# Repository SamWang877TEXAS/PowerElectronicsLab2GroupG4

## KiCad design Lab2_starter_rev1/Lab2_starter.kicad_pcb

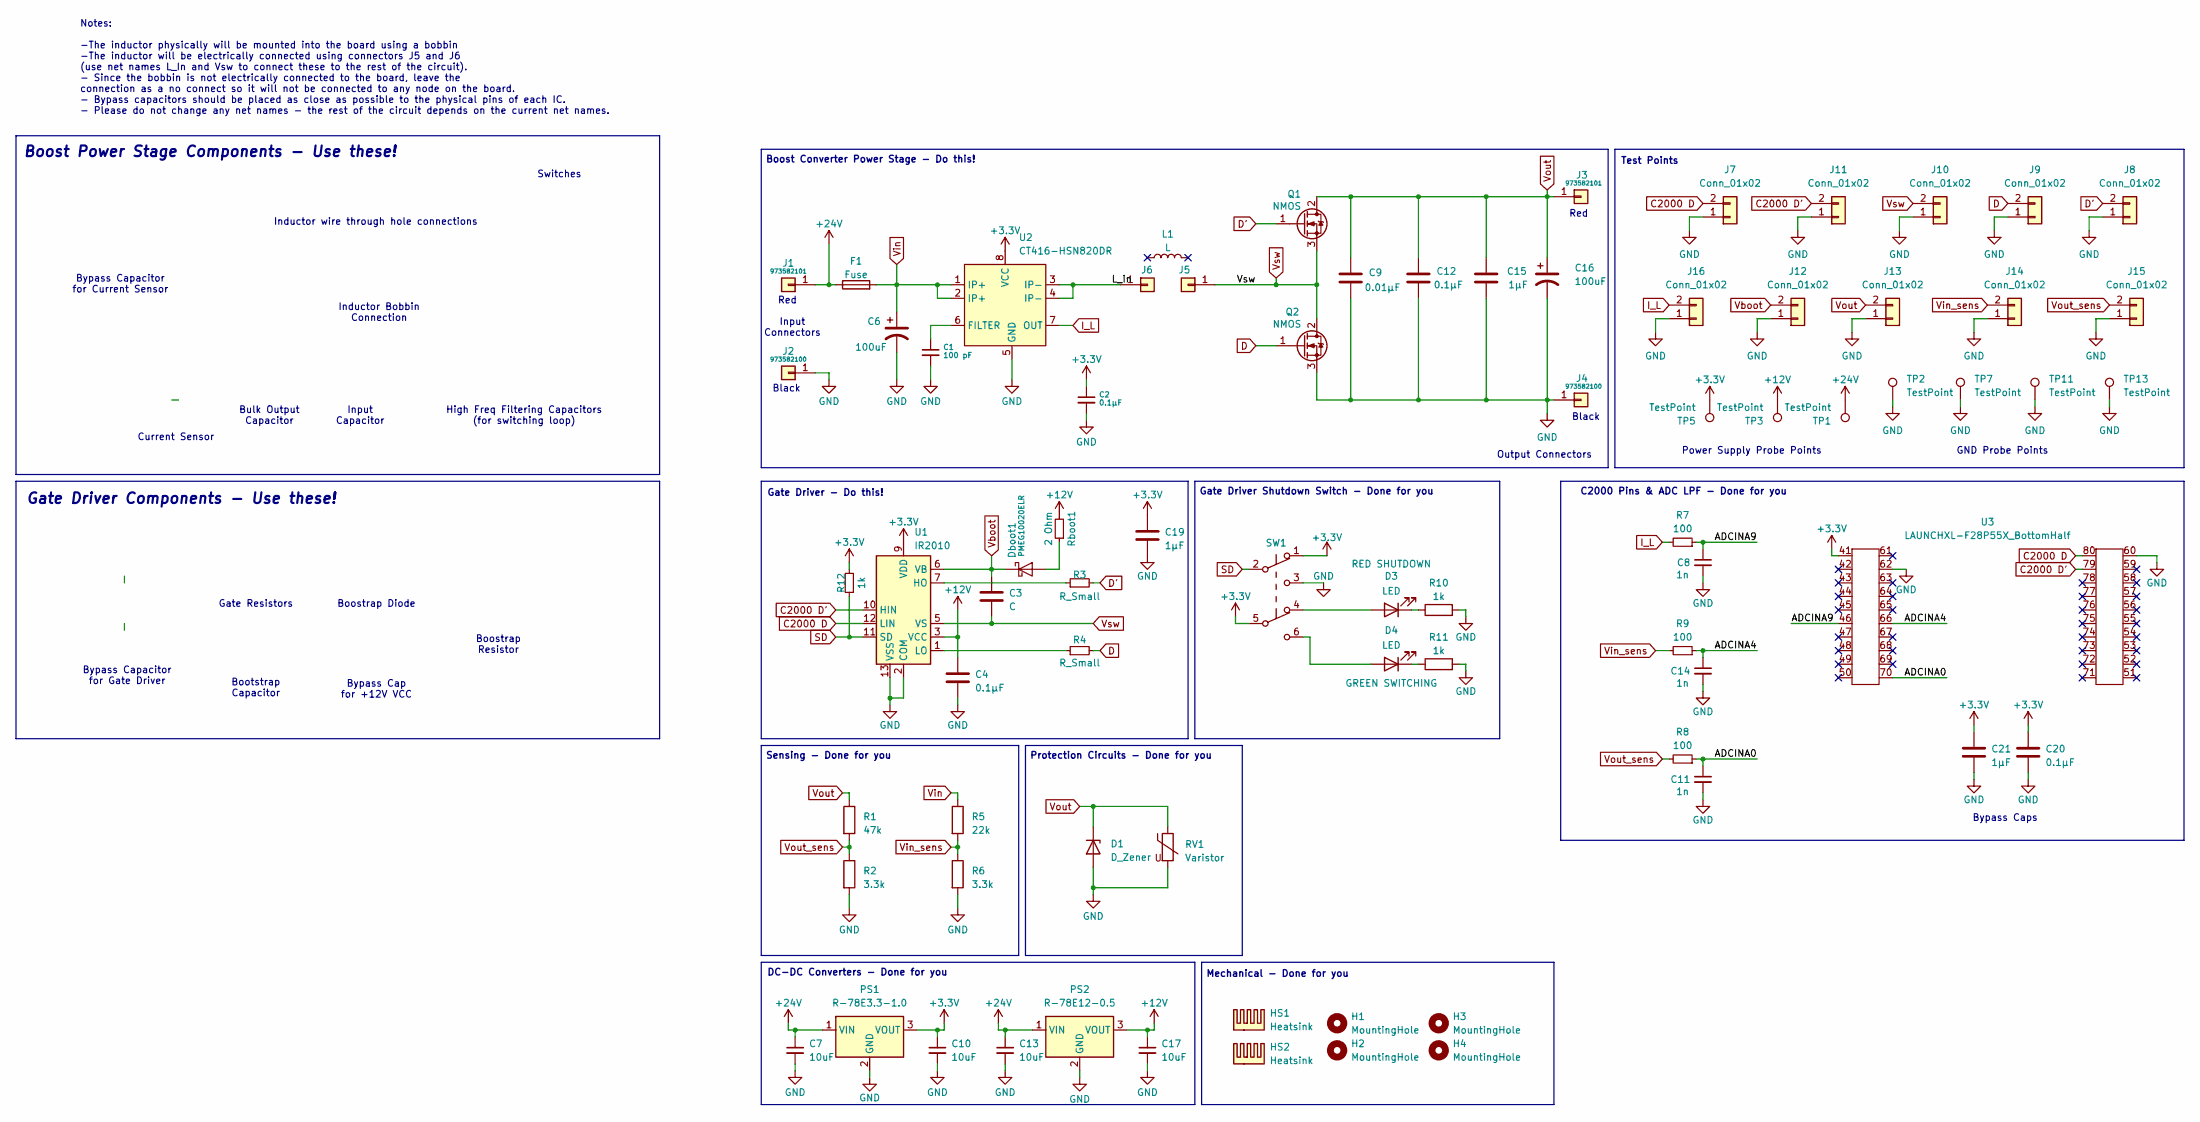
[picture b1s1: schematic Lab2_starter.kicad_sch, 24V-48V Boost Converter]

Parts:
C1: 100 pF; C_0805_2012Metric
C2, C4, C12, C20: 0.1μF; C_0805_2012Metric
C3: C; C_0805_2012Metric
C6, C16: 100uF; 16PX2200MEFC10X20
C7, C10, C13, C17: 10uF; C_0805_2012Metric
C8, C11, C14: 1n; C_0805_2012Metric
C9: 0.01μF; C_0805_2012Metric
C15, C19, C21: 1μF; C_0805_2012Metric
D1: D_Zener; 1.5KE75A
D3, D4: LED; WL-SMRW_1206_REC
Dboot1: PMEG10020ELR; Nexperia_CFP3_SOD-123W
F1: Fuse; 696108003002
H1, H2, H3, H4: MountingHole; MountingHole_3.2mm_M3
HS1, HS2: Heatsink; HSS-B20-NPS-01
J1, J3: 973582101
J2, J4: 973582100
J5, J6: Conn_01x01; Inductor_wire_conn
J7, J8, J9, J10, J11, J12, J13, J14, J15, J16: Conn_01x02; TP
L1: L; Inductor
PS1: R-78E3.3-1.0; PARTREV 6
PS2: R-78E12-0.5; R-78E-0.5_RCP
Q1, Q2: NMOS; TO-220-3_Vertical
R1: 47k; R_0805_2012Metric
R2, R6: 3.3k; R_0805_2012Metric
R3, R4: R_Small; R_0805_2012Metric
R5: 22k; R_0805_2012Metric
R7, R8, R9: 100; R_0805_2012Metric
R10, R11, R12: 1k; R_0805_2012Metric
RV1: Varistor; V100ZA15P
Rboot1: 2 Ohm; R_0805_2012Metric
SW1: SW_Push_DPDT; SLW1116297AD
TP1, TP2, TP3, TP5, TP7, TP11, TP13: TestPoint; TestPoint_Loop_D1.80mm_Drill1.0mm_Beaded
U1: IR2010; 1-2199298-3
U2: CT416-HSN820DR; SOIC-8_3.9x4.9mm_P1.27mm
U3: LAUNCHXL-F28P55X_BottomHalf

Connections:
+3.3V: C2.1, C10.1, C19.1, C20.1, C21.1, PS1.3 (VOUT), R12.2, SW1.1 (A), SW1.5 (B), TP5.1, U1.9 (VDD), U2.8 (VCC), U3.41
+12V: C4.1, C17.1, PS2.3 (VOUT), Rboot1.2, TP3.1, U1.3 (VCC)
+24V: C7.1, C13.1, F1.1, J1.1, PS1.1 (VIN), PS2.1 (VIN), TP1.1
/ADCINA0: C11.1, R8.1, U3.70
/ADCINA4: C14.1, R9.1, U3.66
/ADCINA9: C8.1, R7.1, U3.46
C2000 D: J7.2, U1.12 (LIN), U3.80
C2000 D': J11.2, U1.10 (HIN), U3.79
D: J9.2, Q2.1 (G), R4.2
D': J8.2, Q1.1 (G), R3.2
GND: C1.2, C2.2, C4.2, C6.2, C7.2, C8.2, C9.2, C10.2, C11.2, C12.2, C13.2, C14.2, C15.2, C16.2, C17.2, C19.2, C20.2, C21.2, D1.2 (A), J2.1, J4.1, J7.1, J8.1, J9.1, J10.1, J11.1, J12.1, J13.1, J14.1, J15.1, J16.1, PS1.2 (GND), PS2.2 (GND), Q2.3 (S), R2.2, R6.2, R10.2, R11.2, RV1.2, SW1.3 (C), TP2.1, TP7.1, TP11.1, TP13.1, U1.2 (COM), U1.13 (VSS), U2.5 (GND), U3.60, U3.62
I_L: J16.2, R7.2, U2.7 (OUT)
unnamed: D3.2 (A), SW1.4 (A)
unnamed: D3.1 (K), R10.1
unnamed: D4.2 (A), SW1.6 (C)
unnamed: D4.1 (K), R11.1
unnamed: Dboot1.2 (A), Rboot1.1
unnamed: J6.1, U2.3 (IP-), U2.4 (IP-)
unnamed: R3.1, U1.7 (HO)
unnamed: R4.1, U1.1 (LO)
unnamed: C1.1, U2.6 (FILTER)
SD: R12.1, SW1.2 (B), U1.11 (SD); also elsewhere on the board
Vboot: C3.1, Dboot1.1 (K), J12.2, U1.6 (VB)
Vin: C6.1, F1.2, R5.1, U2.1 (IP+), U2.2 (IP+)
Vin_sens: J14.2, R5.2, R6.1, R9.2
Vout: C9.1, C12.1, C15.1, C16.1, D1.1 (K), J3.1, J13.2, Q1.2 (D), R1.1, RV1.1
Vout_sens: J15.2, R1.2, R2.1, R8.2
Vsw: C3.2, J5.1, J10.2, Q1.3 (S), Q2.2 (D), U1.5 (VS)

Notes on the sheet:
High Freq Filtering Capacitors (for switching loop)
Inductor wire through hole connections
Input Connectors
Sensing - Done for you
Protection Circuits - Done for you
Input Capacitor
Test Points
Bypass Cap for +12V VCC
Black
Mechanical - Done for you
Red
Bulk Output Capacitor
Power Supply Probe Points
Bootstrap Capacitor
Gate Driver Shutdown Switch - Done for you
Notes: -The inductor physically will be mounted into the board using a bobbin -The inductor will be electrically connected using connectors J5 and J6 (use net names L_In and Vsw to connect these to the rest of the circuit). - Since the bobbin is not electrically connected to the board, leave the co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
Gate Driver - Do this!
Current Sensor
Boostrap Resistor
DC-DC Converters - Done for you
Boost Power Stage Components - Use these!
Gate Resistors
C2000 Pins & ADC LPF - Done for you
Boostrap Diode
Output Connectors
Bypass Capacitor for Current Sensor
Inductor Bobbin Connection
Switches
Bypass Capacitor for Gate Driver
Gate Driver Components - Use these!
GND Probe Points
Bypass Caps
Boost Converter Power Stage - Do this!

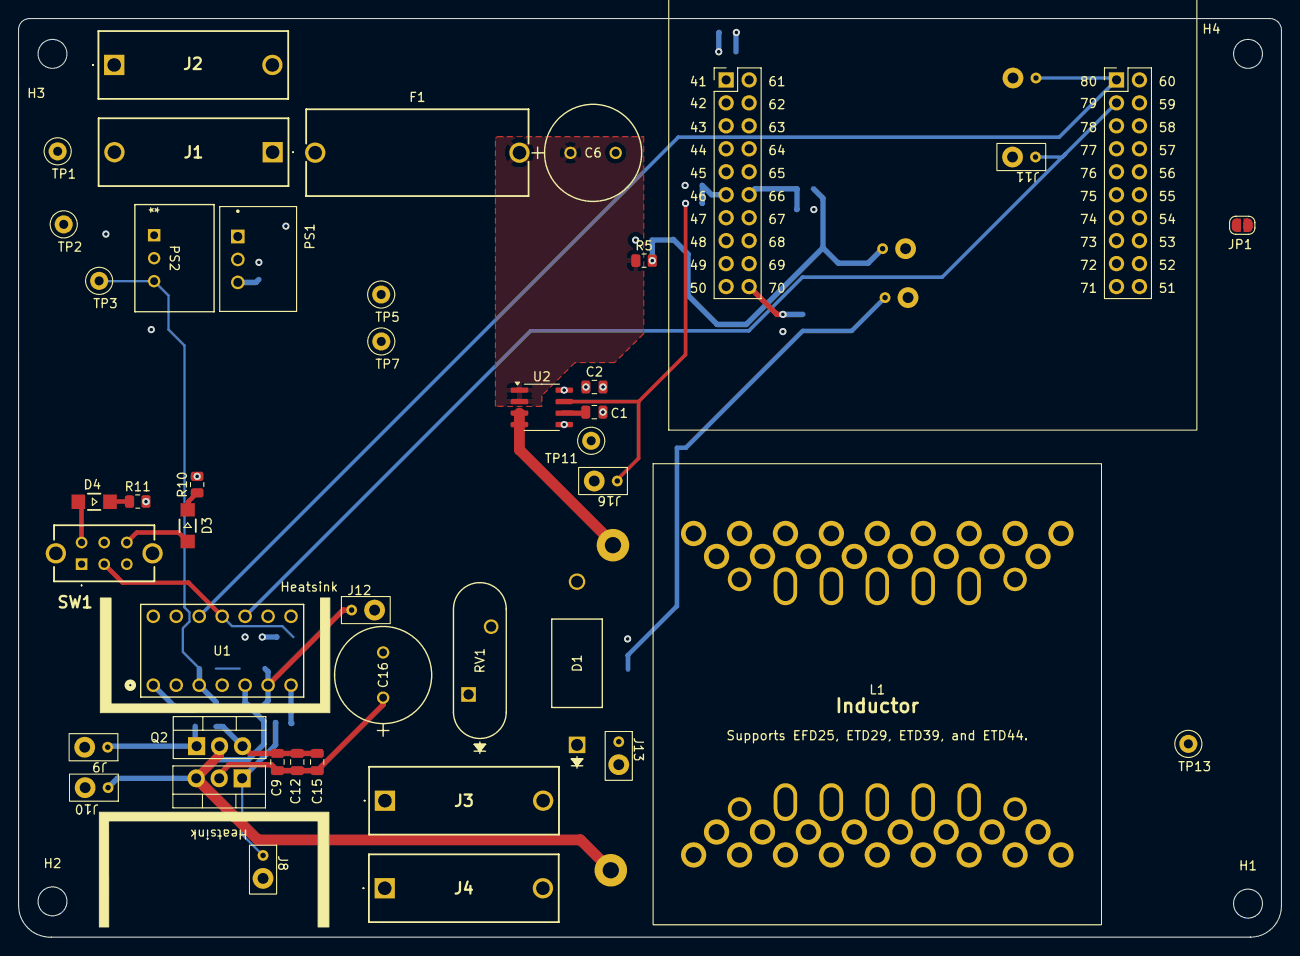
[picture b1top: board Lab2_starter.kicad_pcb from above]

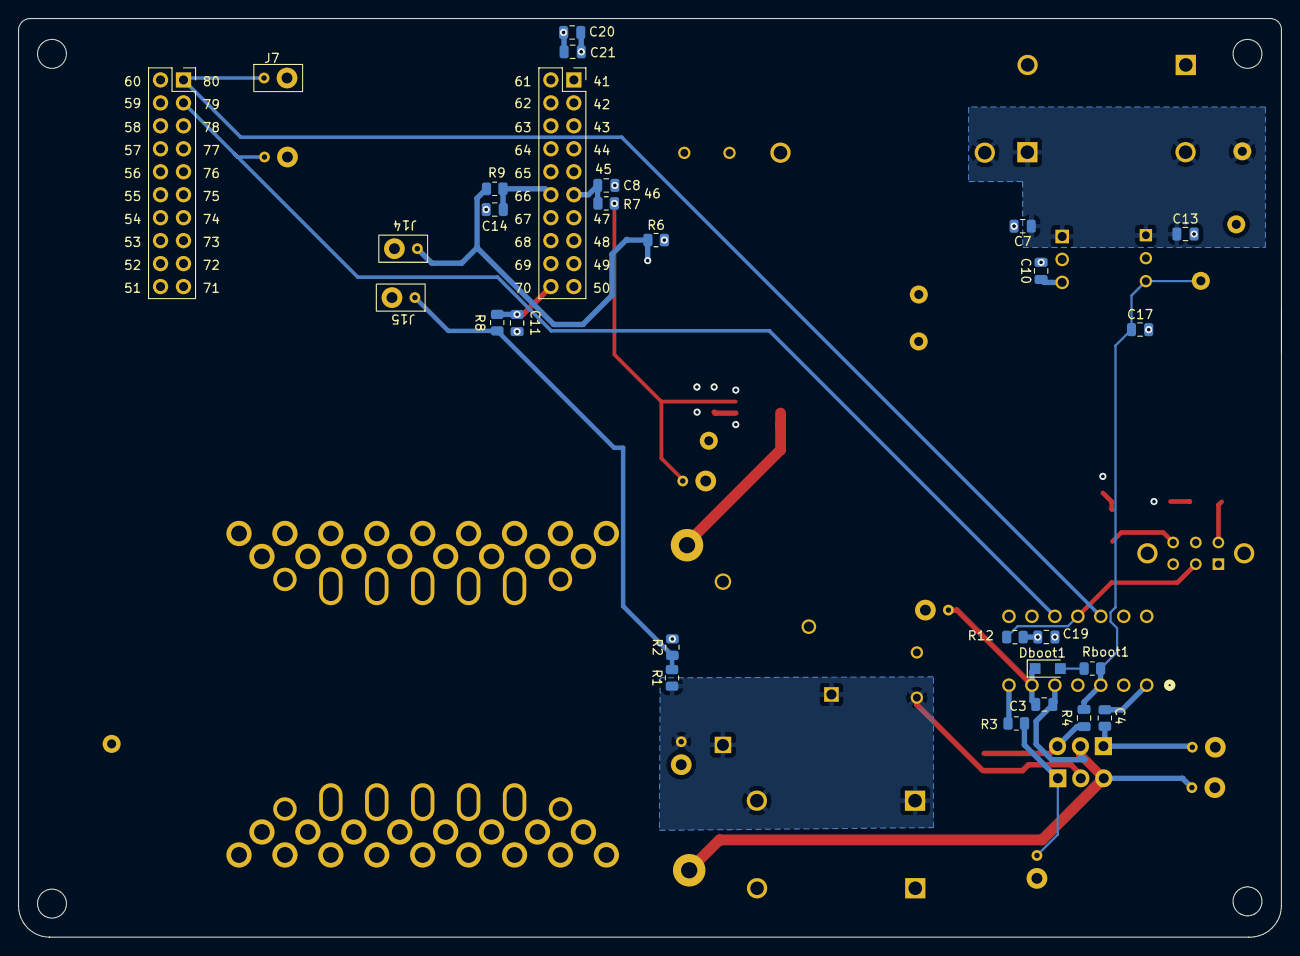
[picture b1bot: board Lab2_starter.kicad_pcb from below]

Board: 4 copper layers, 139.7 x 101.6 mm, 77 parts (26 on the bottom side), 28 nets.

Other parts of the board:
JP1: SolderJumper_2_Open; SolderJumper-2_P1.3mm_Open_RoundedPad1.0x1.5mm

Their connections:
SD: JP1.2 (B); also elsewhere on the board

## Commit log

2025-09-29 First revision for project turn in
2025-09-30 Updated for first PCB upload
    Added missing vias to some grounds
    Increased width of a few wires
    Moved many silkscreens
    Added keepout zone for inductor
2025-10-03 Pre-Design Review Update
2025-10-03 Final Board Revision YAY

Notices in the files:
parts and their libraries:
Copyright 2016 Accelerated Designs. All rights reserved.
